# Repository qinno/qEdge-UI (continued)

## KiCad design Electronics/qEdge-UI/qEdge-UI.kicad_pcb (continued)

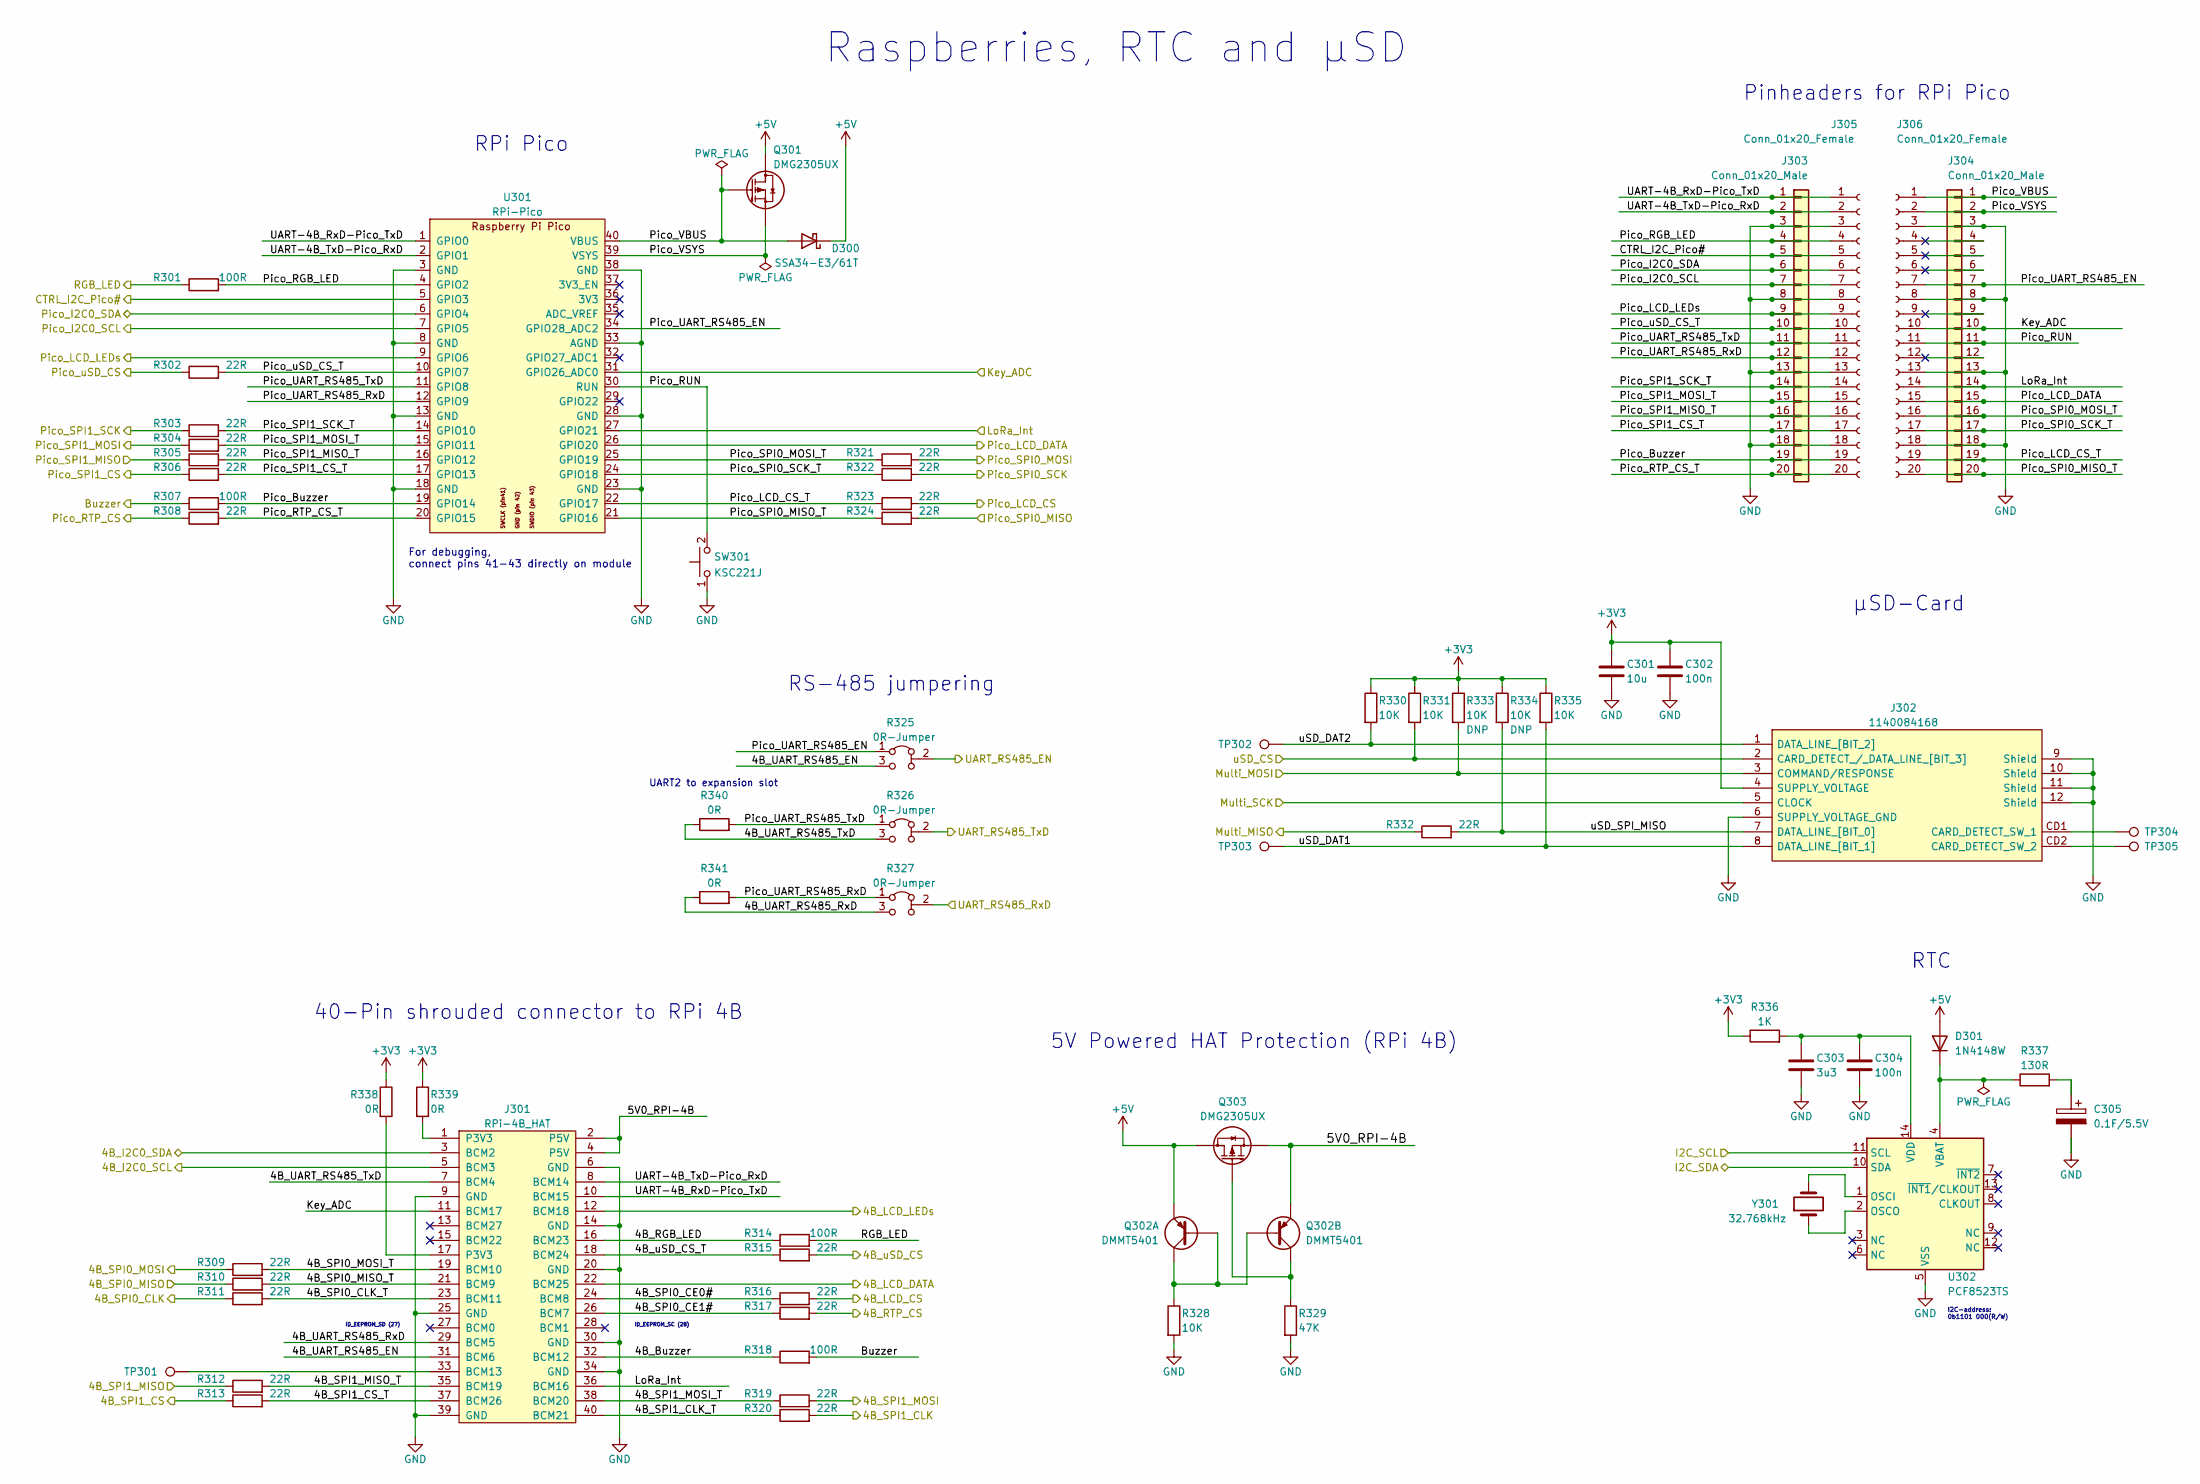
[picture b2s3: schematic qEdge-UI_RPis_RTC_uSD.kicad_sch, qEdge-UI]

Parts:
C301: 10u; C_0603_1608Metric
C302, C304: 100n; C_0603_1608Metric
C303: 3u3; C_0603_1608Metric
C305: 0.1F/5.5V; Elna_DX5R5H104U; Manufacturer_Part_Number DX-5R5H104U
D300: SSA34-E3/61T; D_SMA; Manufacturer_Part_Number SSA34-E3/61T
D301: 1N4148W; D_SOD-123; Manufacturer_Part_Number 1N4148W-E3
J301: RPi-4B_HAT; Wuerth_WR-BHD_61234020621; Manufacturer_Part_Number 61234020621
J302: 1140084168; Amphenol_1140084168; Manufacturer_Part_Number 1140084168
J303, J304: Conn_01x20_Male; PinHeader_1x20_P2.54mm_Vertical; Manufacturer_Part_Number MC34739
J305, J306: Conn_01x20_Female; PinSocket_1x20_P2.54mm_Vertical; Manufacturer_Part_Number 2212S-20SG-85
Q301, Q303: DMG2305UX; SOT-23; Manufacturer_Part_Number DMG2305UX-13
Q302: DMMT5401; SOT-23-6; Manufacturer_Part_Number DMMT5401-7-F
R301, R307, R314, R318: 100R; R_0603_1608Metric
R302, R303, R304, R305, R306, R308, R309, R310, R311, R312, R313, R315, R316, R317, R319, R320, R321, R322, R323, R324, R332: 22R; R_0603_1608Metric
R325, R326, R327: 0R-Jumper; 0603_3-pin-Jumper; Manufacturer_Part_Number RC0603FR-070RL
R328, R330, R331, R333, R334, R335: 10K; R_0603_1608Metric
R329: 47K; R_0603_1608Metric
R336: 1K; R_0603_1608Metric
R337: 130R; R_0603_1608Metric
R338, R339, R340, R341: 0R; R_0603_1608Metric
SW301: KSC221J; SW_Push_1P1T_NO_CK_KSC6xxJ; Manufacturer_Part_Number KSC221JLFS
TP301, TP302, TP303, TP304, TP305: TestPoint; TestPoint_Pad_D1.0mm
U301: RPi-Pico; RPi-Pico_THT_wo_Debug; Manufacturer_Part_Number Pico W
U302: PCF8523TS; TSSOP-14_4.4x5mm_P0.65mm
Y301: 32.768kHz; MicroCrystal_CM7V32768TBQA020; Manufacturer_Part_Number CM7V-T1A-Low-ESR-32.768k-7pF-10-TB-QA

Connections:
+3V3: C301.1, C302.1, J302.4 (SUPPLY_VOLTAGE), R330.1, R331.1, R333.1, R334.1, R335.1, R336.1, R338.1, R339.1; also elsewhere on the board
+5V: D300.1 (K), D301.2 (A), Q301.3 (D), Q302.6 (E), Q303.3 (D); also elsewhere on the board
/Comm. ifaces, Misc/4B_I2C0_SCL: J301.5 (BCM3); also elsewhere on the board
/Comm. ifaces, Misc/4B_I2C0_SDA: J301.3 (BCM2); also elsewhere on the board
/Comm. ifaces, Misc/4B_LCD_CS: R316.2; also elsewhere on the board
/Comm. ifaces, Misc/4B_LCD_DATA: J301.22 (BCM25); also elsewhere on the board
/Comm. ifaces, Misc/4B_LCD_LEDs: J301.12 (BCM18); also elsewhere on the board
/Comm. ifaces, Misc/4B_RTP_CS: R317.2; also elsewhere on the board
/Comm. ifaces, Misc/4B_SPI0_MISO: R310.1; also elsewhere on the board
/Comm. ifaces, Misc/4B_SPI0_MOSI: R309.1; also elsewhere on the board
/Comm. ifaces, Misc/4B_SPI0_SCK: R311.1; also elsewhere on the board
/Comm. ifaces, Misc/4B_SPI1_CS: R313.1; also elsewhere on the board
/Comm. ifaces, Misc/4B_SPI1_MISO: R312.1; also elsewhere on the board
/Comm. ifaces, Misc/4B_SPI1_MOSI: R319.2; also elsewhere on the board
/Comm. ifaces, Misc/4B_SPI1_SCK: R320.2; also elsewhere on the board
/Comm. ifaces, Misc/4B_uSD_CS: R315.2; also elsewhere on the board
/Comm. ifaces, Misc/I2C_SCL: U302.11 (SCL); also elsewhere on the board
/Comm. ifaces, Misc/I2C_SDA: U302.10 (SDA); also elsewhere on the board
/Comm. ifaces, Misc/Multi_MISO: R332.1; also elsewhere on the board
/Comm. ifaces, Misc/Multi_MOSI: J302.3 (COMMAND/RESPONSE), R333.2; also elsewhere on the board
/Comm. ifaces, Misc/Multi_SCK: J302.5 (CLOCK); also elsewhere on the board
/Comm. ifaces, Misc/Pico_LCD_CS: R323.2; also elsewhere on the board
/Comm. ifaces, Misc/Pico_RTP_CS: R308.1; also elsewhere on the board
/Comm. ifaces, Misc/Pico_SPI0_MISO: R324.2; also elsewhere on the board
/Comm. ifaces, Misc/Pico_SPI0_MOSI: R321.2; also elsewhere on the board
/Comm. ifaces, Misc/Pico_SPI0_SCK: R322.2; also elsewhere on the board
/Comm. ifaces, Misc/Pico_SPI1_CS: R306.1; also elsewhere on the board
/Comm. ifaces, Misc/Pico_SPI1_MISO: R305.1; also elsewhere on the board
/Comm. ifaces, Misc/Pico_SPI1_MOSI: R304.1; also elsewhere on the board
/Comm. ifaces, Misc/Pico_SPI1_SCK: R303.1; also elsewhere on the board
/Comm. ifaces, Misc/Pico_uSD_CS: R302.1; also elsewhere on the board
/Comm. ifaces, Misc/UART_RS485_EN: R325.2 (B); also elsewhere on the board
/Comm. ifaces, Misc/UART_RS485_RxD: R327.2 (B); also elsewhere on the board
/Comm. ifaces, Misc/UART_RS485_TxD: R326.2 (B); also elsewhere on the board
/Comm. ifaces, Misc/uSD_CS: J302.2 (CARD_DETECT_/_DATA_LINE_[BIT_3]), R331.2; also elsewhere on the board
/RPis, RTC, µSD/4B_Buzzer: J301.32 (BCM12), R318.1
/RPis, RTC, µSD/4B_RGB_LED: J301.16 (BCM23), R314.1
/RPis, RTC, µSD/4B_SPI0_CE0#: J301.24 (BCM8), R316.1
/RPis, RTC, µSD/4B_SPI0_CE1#: J301.26 (BCM7), R317.1
/RPis, RTC, µSD/4B_SPI0_CLK_T: J301.23 (BCM11), R311.2
/RPis, RTC, µSD/4B_SPI0_MISO_T: J301.21 (BCM9), R310.2
/RPis, RTC, µSD/4B_SPI0_MOSI_T: J301.19 (BCM10), R309.2
/RPis, RTC, µSD/4B_SPI1_CLK_T: J301.40 (BCM21), R320.1
/RPis, RTC, µSD/4B_SPI1_CS_T: J301.37 (BCM26), R313.2
/RPis, RTC, µSD/4B_SPI1_MISO_T: J301.35 (BCM19), R312.2
/RPis, RTC, µSD/4B_SPI1_MOSI_T: J301.38 (BCM20), R319.1
/RPis, RTC, µSD/4B_UART_RS485_EN: J301.31 (BCM6), R325.3 (C)
/RPis, RTC, µSD/4B_UART_RS485_RxD: J301.29 (BCM5), R327.3 (C), R341.1
/RPis, RTC, µSD/4B_UART_RS485_TxD: J301.7 (BCM4), R326.3 (C), R340.1
/RPis, RTC, µSD/4B_uSD_CS_T: J301.18 (BCM24), R315.1
/RPis, RTC, µSD/5V0_RPI-4B: J301.2 (P5V), J301.4 (P5V), Q302.5 (E), Q303.2 (S)
/RPis, RTC, µSD/Buzzer: R307.1, R318.2; also elsewhere on the board
/RPis, RTC, µSD/CTRL_I2C_Pico#: J303.5, J305.5, U301.5 (GPIO3); also elsewhere on the board
/RPis, RTC, µSD/Key_ADC: J301.11 (BCM17), J304.10, J306.10, U301.31 (GPIO26_ADC0); also elsewhere on the board
/RPis, RTC, µSD/LoRa_Int: J301.36 (BCM16), J304.14, J306.14, U301.27 (GPIO21); also elsewhere on the board
/RPis, RTC, µSD/Pico_Buzzer: J303.19, J305.19, R307.2, U301.19 (GPIO14)
/RPis, RTC, µSD/Pico_I2C0_SCL: J303.7, J305.7, U301.7 (GPIO5); also elsewhere on the board
/RPis, RTC, µSD/Pico_I2C0_SDA: J303.6, J305.6, U301.6 (GPIO4); also elsewhere on the board
/RPis, RTC, µSD/Pico_LCD_CS_T: J304.19, J306.19, R323.1, U301.22 (GPIO17)
/RPis, RTC, µSD/Pico_LCD_DATA: J304.15, J306.15, U301.26 (GPIO20); also elsewhere on the board
/RPis, RTC, µSD/Pico_LCD_LEDs: J303.9, J305.9, U301.9 (GPIO6); also elsewhere on the board
/RPis, RTC, µSD/Pico_RGB_LED: J303.4, J305.4, R301.2, U301.4 (GPIO2)
/RPis, RTC, µSD/Pico_RTP_CS_T: J303.20, J305.20, R308.2, U301.20 (GPIO15)
/RPis, RTC, µSD/Pico_RUN: J304.11, J306.11, SW301.2, U301.30 (RUN)
/RPis, RTC, µSD/Pico_SPI0_MISO_T: J304.20, J306.20, R324.1, U301.21 (GPIO16)
/RPis, RTC, µSD/Pico_SPI0_MOSI_T: J304.16, J306.16, R321.1, U301.25 (GPIO19)
/RPis, RTC, µSD/Pico_SPI0_SCK_T: J304.17, J306.17, R322.1, U301.24 (GPIO18)
/RPis, RTC, µSD/Pico_SPI1_CS_T: J303.17, J305.17, R306.2, U301.17 (GPIO13)
/RPis, RTC, µSD/Pico_SPI1_MISO_T: J303.16, J305.16, R305.2, U301.16 (GPIO12)
/RPis, RTC, µSD/Pico_SPI1_MOSI_T: J303.15, J305.15, R304.2, U301.15 (GPIO11)
/RPis, RTC, µSD/Pico_SPI1_SCK_T: J303.14, J305.14, R303.2, U301.14 (GPIO10)
/RPis, RTC, µSD/Pico_UART_RS485_EN: J304.7, J306.7, R325.1 (A), U301.34 (GPIO28_ADC2)
/RPis, RTC, µSD/Pico_UART_RS485_RxD: J303.12, J305.12, R327.1 (A), R341.2, U301.12 (GPIO9)
/RPis, RTC, µSD/Pico_UART_RS485_TxD: J303.11, J305.11, R326.1 (A), R340.2, U301.11 (GPIO8)
/RPis, RTC, µSD/Pico_VBUS: D300.2 (A), J304.1, J306.1, Q301.1 (G), U301.40 (VBUS)
/RPis, RTC, µSD/Pico_VSYS: J304.2, J306.2, Q301.2 (S), U301.39 (VSYS)
/RPis, RTC, µSD/Pico_uSD_CS_T: J303.10, J305.10, R302.2, U301.10 (GPIO7)
/RPis, RTC, µSD/RGB_LED: R301.1, R314.2; also elsewhere on the board
/RPis, RTC, µSD/UART-4B_RxD-Pico_TxD: J301.10 (BCM15), J303.1, J305.1, U301.1 (GPIO0)
/RPis, RTC, µSD/UART-4B_TxD-Pico_RxD: J301.8 (BCM14), J303.2, J305.2, U301.2 (GPIO1)
/RPis, RTC, µSD/uSD_DAT1: J302.8 (DATA_LINE_[BIT_1]), R335.2, TP303.1
/RPis, RTC, µSD/uSD_DAT2: J302.1 (DATA_LINE_[BIT_2]), R330.2, TP302.1
/RPis, RTC, µSD/uSD_SPI_MISO: J302.7 (DATA_LINE_[BIT_0]), R332.2, R334.2
GND: C301.2, C302.2, C303.2, C304.2, C305.1, J301.6 (GND), J301.9 (GND), J301.14 (GND), J301.20 (GND), J301.25 (GND), J301.30 (GND), J301.34 (GND), J301.39 (GND), J302.6 (SUPPLY_VOLTAGE_GND), J302.9 (Shield), J302.10 (Shield), J302.11 (Shield), J302.12 (Shield), J303.3, J303.8, J303.13, J303.18, J304.3, J304.8, J304.13, J304.18, J305.3, J305.8, J305.13, J305.18, J306.3, J306.8, J306.13, J306.18, R328.2, R329.2, SW301.1, U301.3 (GND), U301.8 (GND), U301.13 (GND), U301.18 (GND), U301.23 (GND), U301.28 (GND), U301.33 (AGND), U301.38 (GND), U302.5 (VSS); also elsewhere on the board
unnamed: C303.1, C304.1, R336.2, U302.14 (VDD)
unnamed: C305.2, R337.2
unnamed: D301.1 (K), R337.1, U302.4 (VBAT)
unnamed: J301.1 (P3V3), R339.2
unnamed: J301.17 (P3V3), R338.2
unnamed: J301.33 (BCM13), TP301.1
unnamed: J302.CD1 (CARD_DETECT_SW_1), TP304.1
unnamed: J302.CD2 (CARD_DETECT_SW_2), TP305.1
unnamed: Q302.1 (C), Q302.2 (B), Q302.3 (B), R328.1
unnamed: Q302.4 (C), Q303.1 (G), R329.1
unnamed: U302.1 (OSCI), Y301.2
unnamed: U302.2 (OSCO), Y301.1

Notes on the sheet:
Pinheaders for RPi Pico
ID_EEPROM_SC (28)
RS-485 jumpering
For debugging, connect pins 41-43 directly on module
µSD-Card
ID_EEPROM_SD (27)
RTC
RPi Pico
5V Powered HAT Protection (RPi 4B)
I2C-address: 0b1101 000(R/W)
UART2 to expansion slot
40-Pin shrouded connector to RPi 4B
Raspberries, RTC and µSD

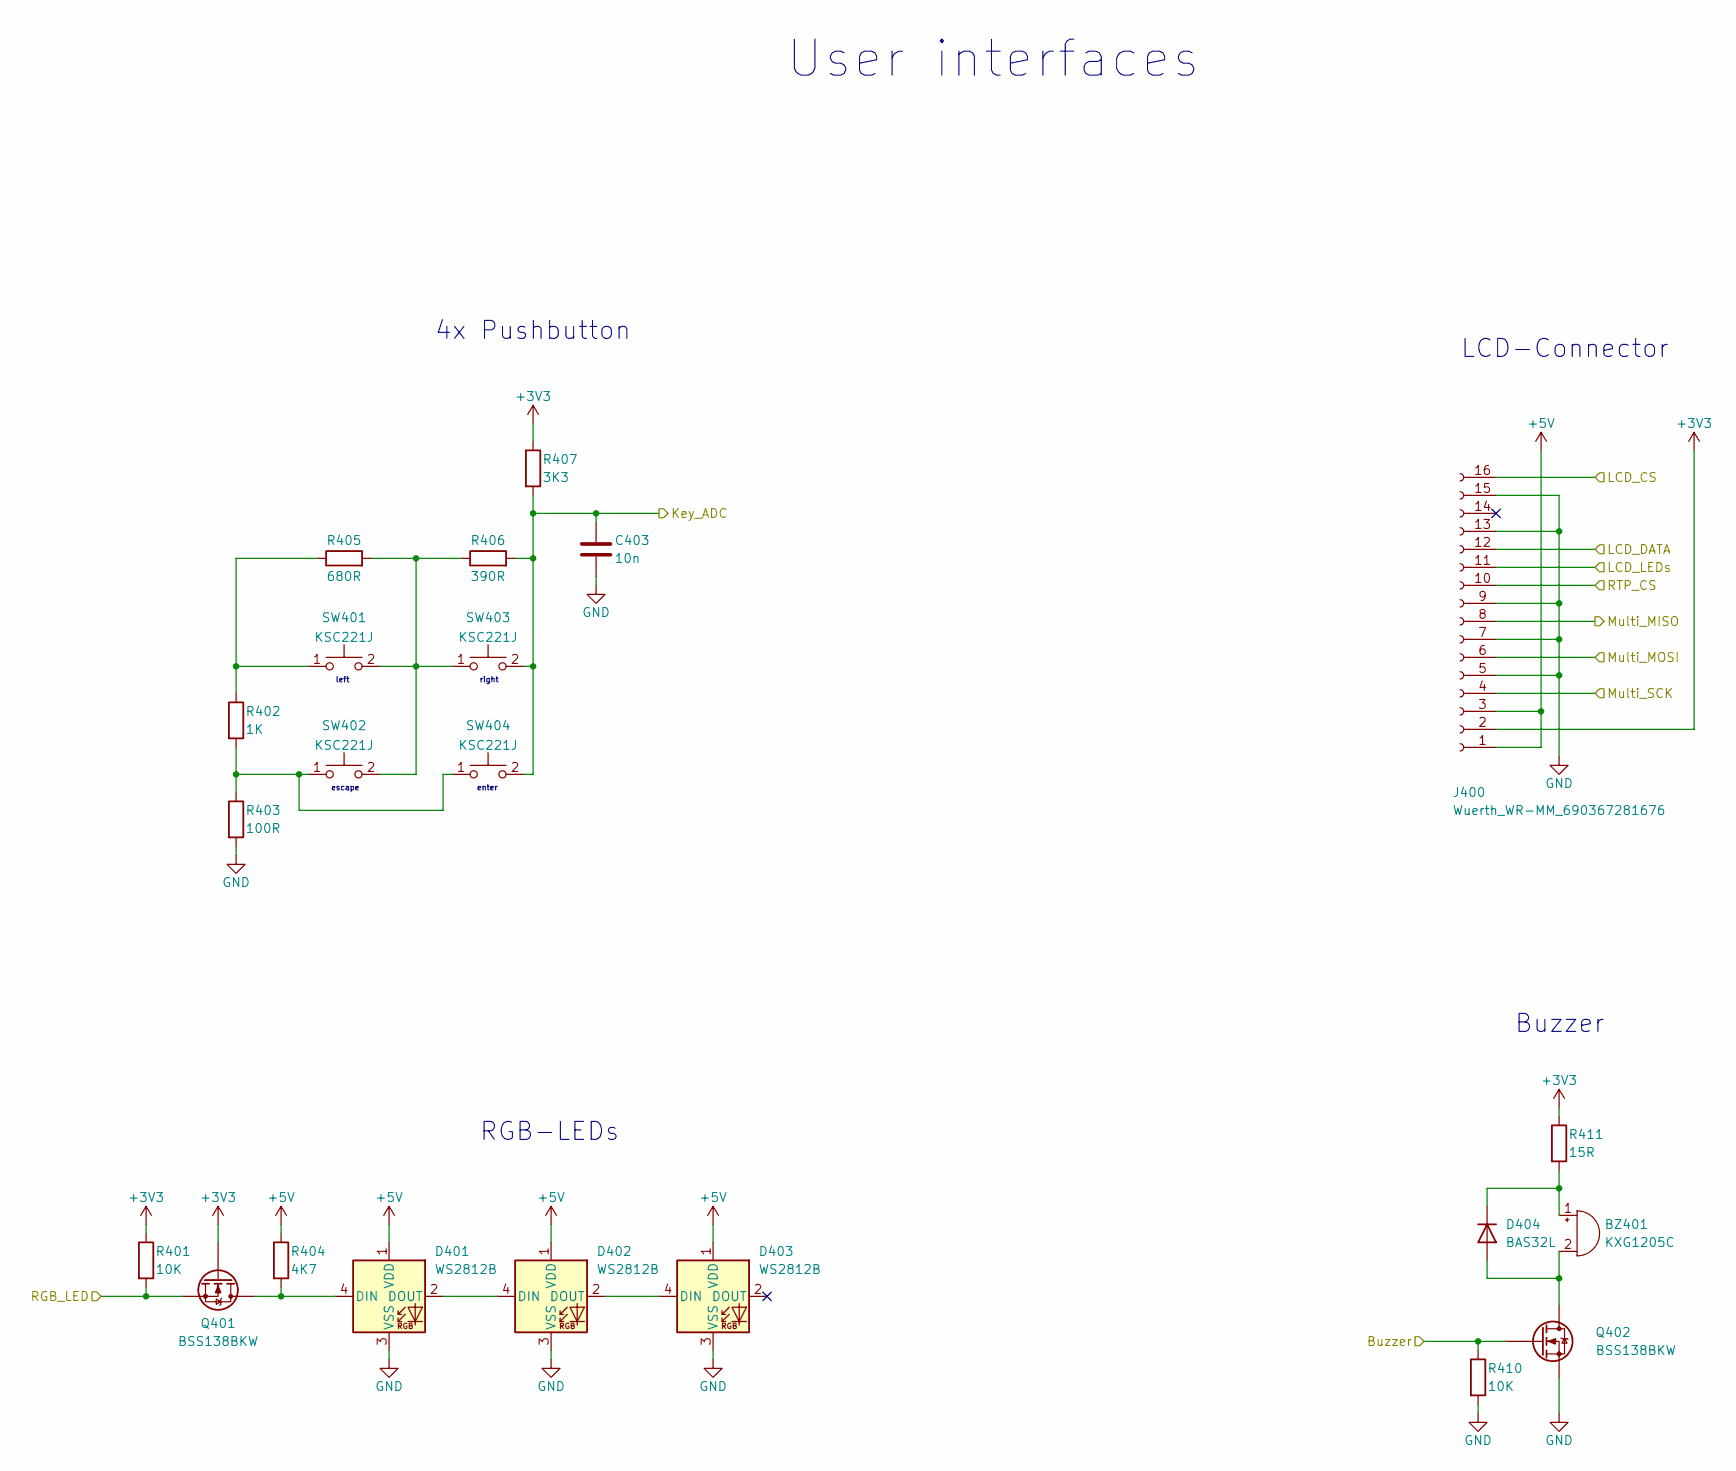
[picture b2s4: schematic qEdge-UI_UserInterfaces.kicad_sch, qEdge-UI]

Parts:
BZ401: KXG1205C; Buzzer_12x9.5RM7.6; Manufacturer_Part_Number KXG1205C
C403: 10n; C_0603_1608Metric
D401, D402, D403: WS2812B; LED_WS2812B_PLCC4_5.0x5.0mm_P3.2mm; Manufacturer_Part_Number WS2812B
D404: BAS32L; D_MiniMELF; Manufacturer_Part_Number BAS32L,115
J400: Wuerth_WR-MM_690367281676; Manufacturer_Part_Number 690367281676
Q401, Q402: BSS138BKW; SOT-323_SC-70; Manufacturer_Part_Number BSS138BKW,115
R401, R410: 10K; R_0603_1608Metric
R402: 1K; R_0603_1608Metric
R403: 100R; R_0603_1608Metric
R404: 4K7; R_0603_1608Metric
R405: 680R; R_0603_1608Metric
R406: 390R; R_0603_1608Metric
R407: 3K3; R_0603_1608Metric
R411: 15R; R_0805_2012Metric
SW401, SW402, SW403, SW404: KSC221J; SW_Push_1P1T_NO_CK_KSC6xxJ; Manufacturer_Part_Number KSC221JLFS

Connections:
+3V3: J400.2, Q401.1 (G), R401.1, R407.1, R411.1; also elsewhere on the board
+5V: D401.1 (VDD), D402.1 (VDD), D403.1 (VDD), J400.1, J400.3, R404.1; also elsewhere on the board
/Comm. ifaces, Misc/LCD_CS: J400.16; also elsewhere on the board
/Comm. ifaces, Misc/LCD_DATA: J400.12; also elsewhere on the board
/Comm. ifaces, Misc/LCD_LEDs: J400.11; also elsewhere on the board
/Comm. ifaces, Misc/Multi_MISO: J400.8; also elsewhere on the board
/Comm. ifaces, Misc/Multi_MOSI: J400.6; also elsewhere on the board
/Comm. ifaces, Misc/Multi_SCK: J400.4; also elsewhere on the board
/Comm. ifaces, Misc/RTP_CS: J400.10; also elsewhere on the board
/RPis, RTC, µSD/Buzzer: Q402.1 (G), R410.1; also elsewhere on the board
/RPis, RTC, µSD/Key_ADC: C403.1, R406.2, R407.2, SW403.2, SW404.2; also elsewhere on the board
/RPis, RTC, µSD/RGB_LED: Q401.2 (S), R401.2; also elsewhere on the board
GND: C403.2, D401.3 (VSS), D402.3 (VSS), D403.3 (VSS), J400.5, J400.7, J400.9, J400.13, J400.15, Q402.2 (S), R403.2, R410.2; also elsewhere on the board
unnamed: BZ401.1 (-), D404.1 (K), R411.2
unnamed: BZ401.2 (+), D404.2 (A), Q402.3 (D)
unnamed: D401.2 (DOUT), D402.4 (DIN)
unnamed: D401.4 (DIN), Q401.3 (D), R404.2
unnamed: D402.2 (DOUT), D403.4 (DIN)
unnamed: R402.1, R405.1, SW401.1
unnamed: R402.2, R403.1, SW402.1, SW404.1
unnamed: R405.2, R406.1, SW401.2, SW402.2, SW403.1

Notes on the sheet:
right
left
escape
Buzzer
User interfaces
LCD-Connector
4x Pushbutton
enter
RGB-LEDs

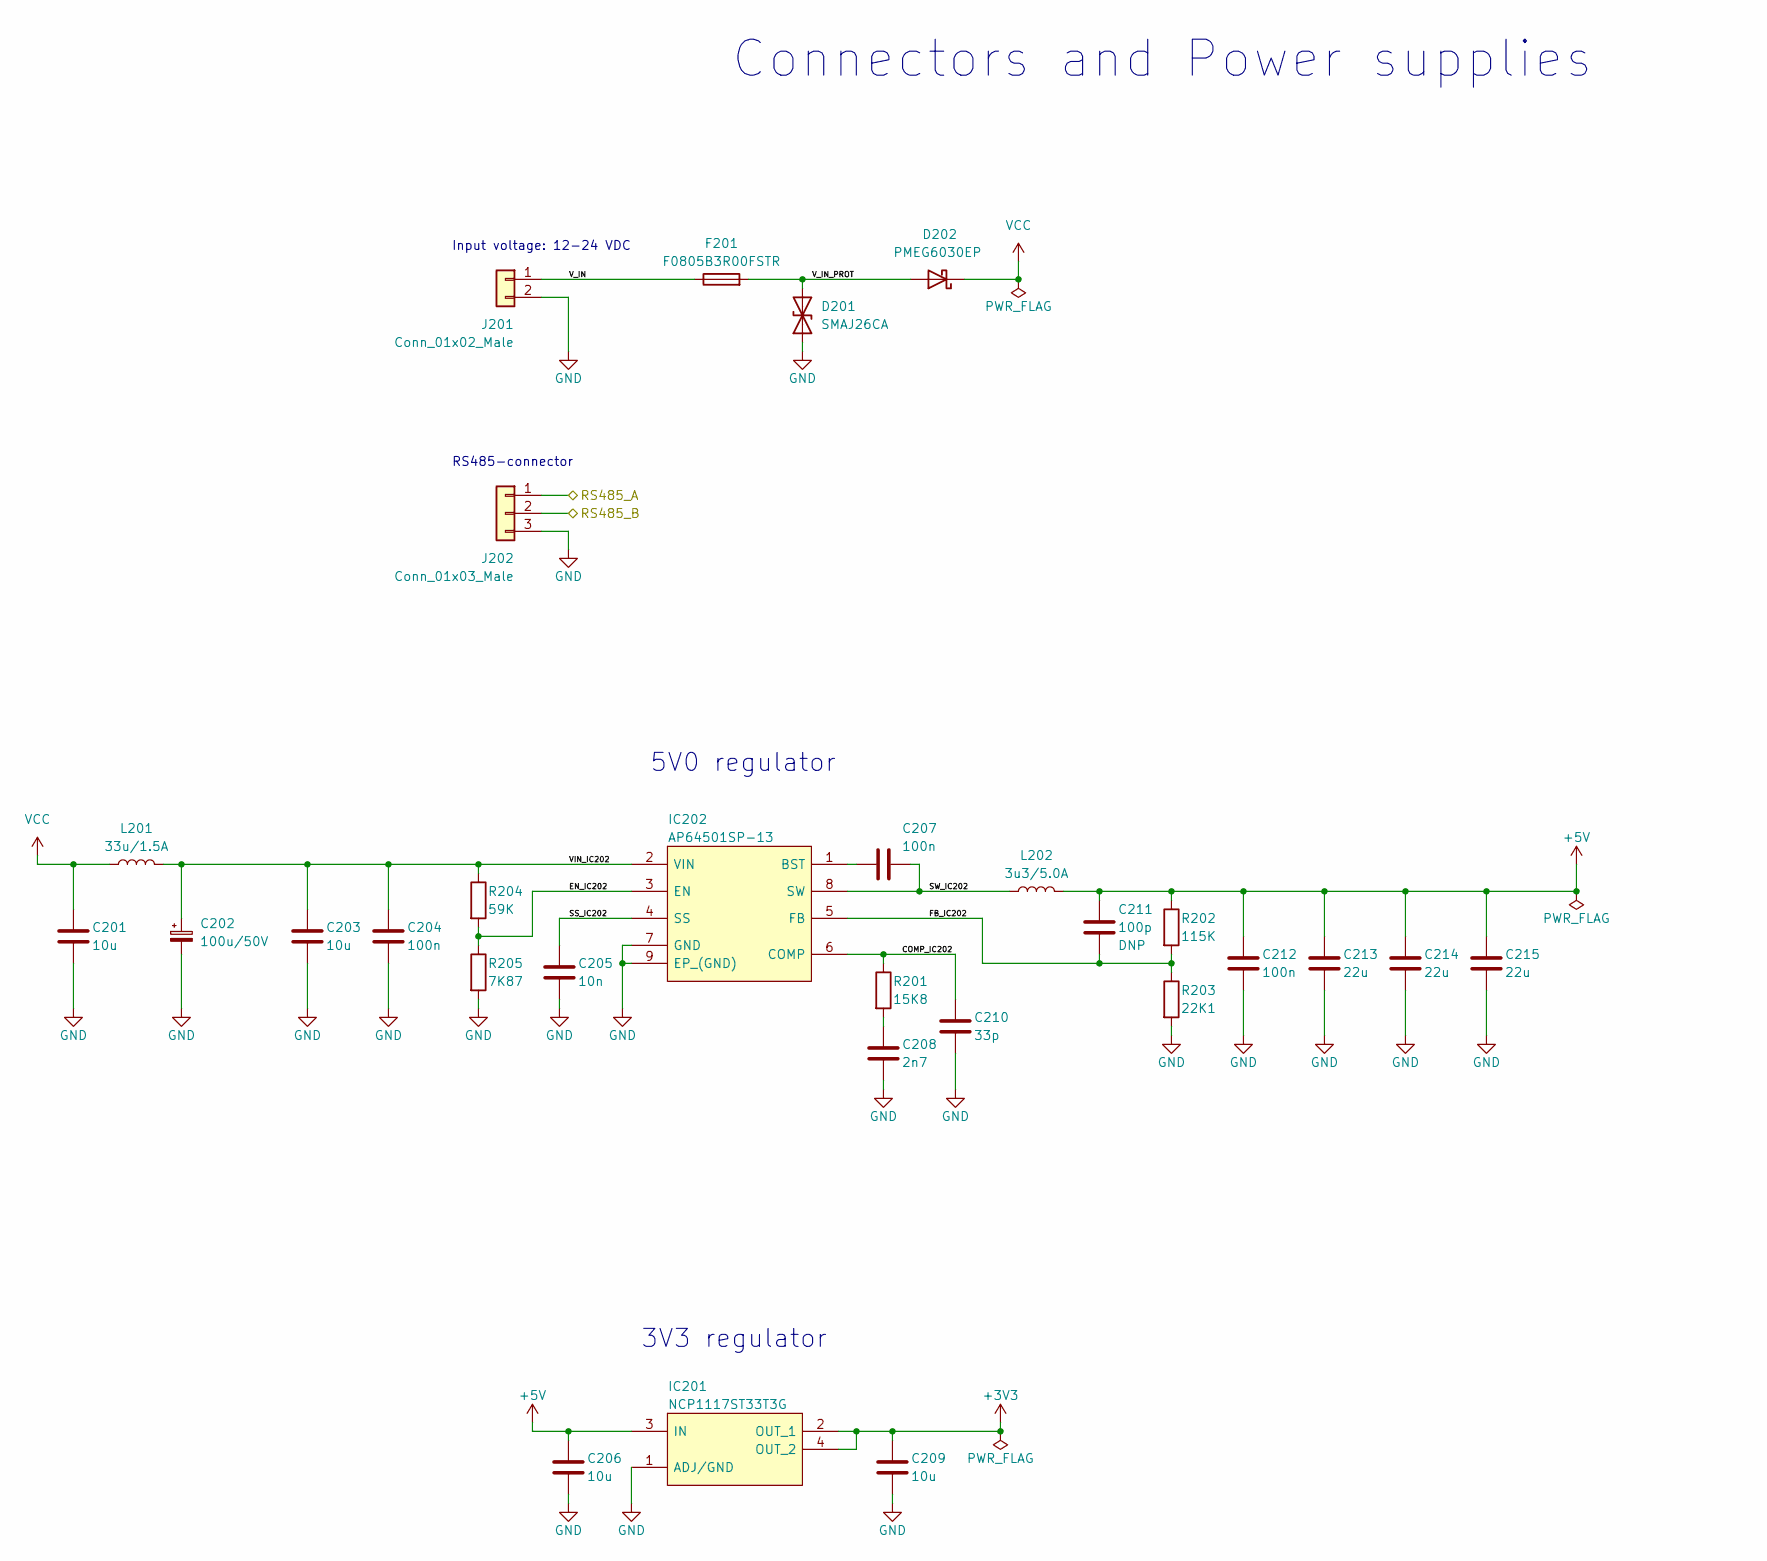
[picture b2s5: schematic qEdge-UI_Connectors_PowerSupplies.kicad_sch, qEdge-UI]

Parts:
C201, C203: 10u; C_0805_2012Metric
C202: 100u/50V; CP_Elec_8x10.5; Manufacturer_Part_Number 865080653016
C204, C207, C212: 100n; C_0603_1608Metric
C205: 10n; C_0603_1608Metric
C206, C209: 10u; C_0603_1608Metric
C208: 2n7; C_0603_1608Metric
C210: 33p; C_0603_1608Metric
C211: 100p; C_0603_1608Metric
C213, C214, C215: 22u; C_0805_2012Metric
D201: SMAJ26CA; D_SMA_bipolar; Manufacturer_Part_Number SMAJ26CA
D202: PMEG6030EP; D_SOD-128; Manufacturer_Part_Number PMEG6030EP,115
F201: F0805B3R00FSTR; Fuse_0805_2012Metric; Manufacturer_Part_Number F0805B3R00FSTR
IC201: NCP1117ST33T3G; SOT230P700X180-4N; Manufacturer_Part_Number NCP1117ST33T3G
IC202: AP64501SP-13; SOIC127P600X163-9N; Manufacturer_Part_Number AP64501SP-13
J201: Conn_01x02_Male; PhoenixContact_MC_1,5_2-G-3.5_1x02_P3.50mm_Horizontal; Manufacturer_Part_Number MC 1,5/ 2-G-3,5 - 1844210
J202: Conn_01x03_Male; PhoenixContact_MC_1,5_3-G-3.5_1x03_P3.50mm_Horizontal; Manufacturer_Part_Number MC 1,5/ 3-G-3,5 - 1844223
L201: 33u/1.5A; Murata_1255AY100MP3; Manufacturer_Part_Number 1255AY-330M=P3
L202: 3u3/5.0A; Abracon_ASPI0530LR3R3MT2; Manufacturer_Part_Number ASPI-0530LR-3R3M-T2
R201: 15K8; R_0603_1608Metric
R202: 115K; R_0603_1608Metric
R203: 22K1; R_0603_1608Metric
R204: 59K; R_0603_1608Metric
R205: 7K87; R_0603_1608Metric

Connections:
+3V3: C209.1, IC201.2 (OUT_1), IC201.4 (OUT_2); also elsewhere on the board
+5V: C206.1, C211.1, C212.1, C213.1, C214.1, C215.1, IC201.3 (IN), L202.2, R202.1; also elsewhere on the board
/Comm. ifaces, Misc/RS485_A: J202.1; also elsewhere on the board
/Comm. ifaces, Misc/RS485_B: J202.2; also elsewhere on the board
/Connectors, Power supplies/COMP_IC202: C210.1, IC202.6 (COMP), R201.1
/Connectors, Power supplies/EN_IC202: IC202.3 (EN), R204.2, R205.1
/Connectors, Power supplies/FB_IC202: C211.2, IC202.5 (FB), R202.2, R203.1
/Connectors, Power supplies/SS_IC202: C205.1, IC202.4 (SS)
/Connectors, Power supplies/SW_IC202: C207.1, IC202.8 (SW), L202.1
/Connectors, Power supplies/VIN_IC202: C202.1, C203.1, C204.1, IC202.2 (VIN), L201.2, R204.1
/Connectors, Power supplies/V_IN: F201.1, J201.1
/Connectors, Power supplies/V_IN_PROT: D201.2 (A2), D202.2 (A), F201.2
GND: C201.2, C202.2, C203.2, C204.2, C205.2, C206.2, C208.2, C209.2, C210.2, C212.2, C213.2, C214.2, C215.2, D201.1 (A1), IC201.1 (ADJ/GND), IC202.7 (GND), IC202.9 (EP_(GND)), J201.2, J202.3, R203.2, R205.2; also elsewhere on the board
unnamed: C207.2, IC202.1 (BST)
unnamed: C208.1, R201.2
VCC: C201.1, D202.1 (K), L201.1

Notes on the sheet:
RS485-connector
Connectors and Power supplies
3V3 regulator
5V0 regulator
Input voltage: 12-24 VDC

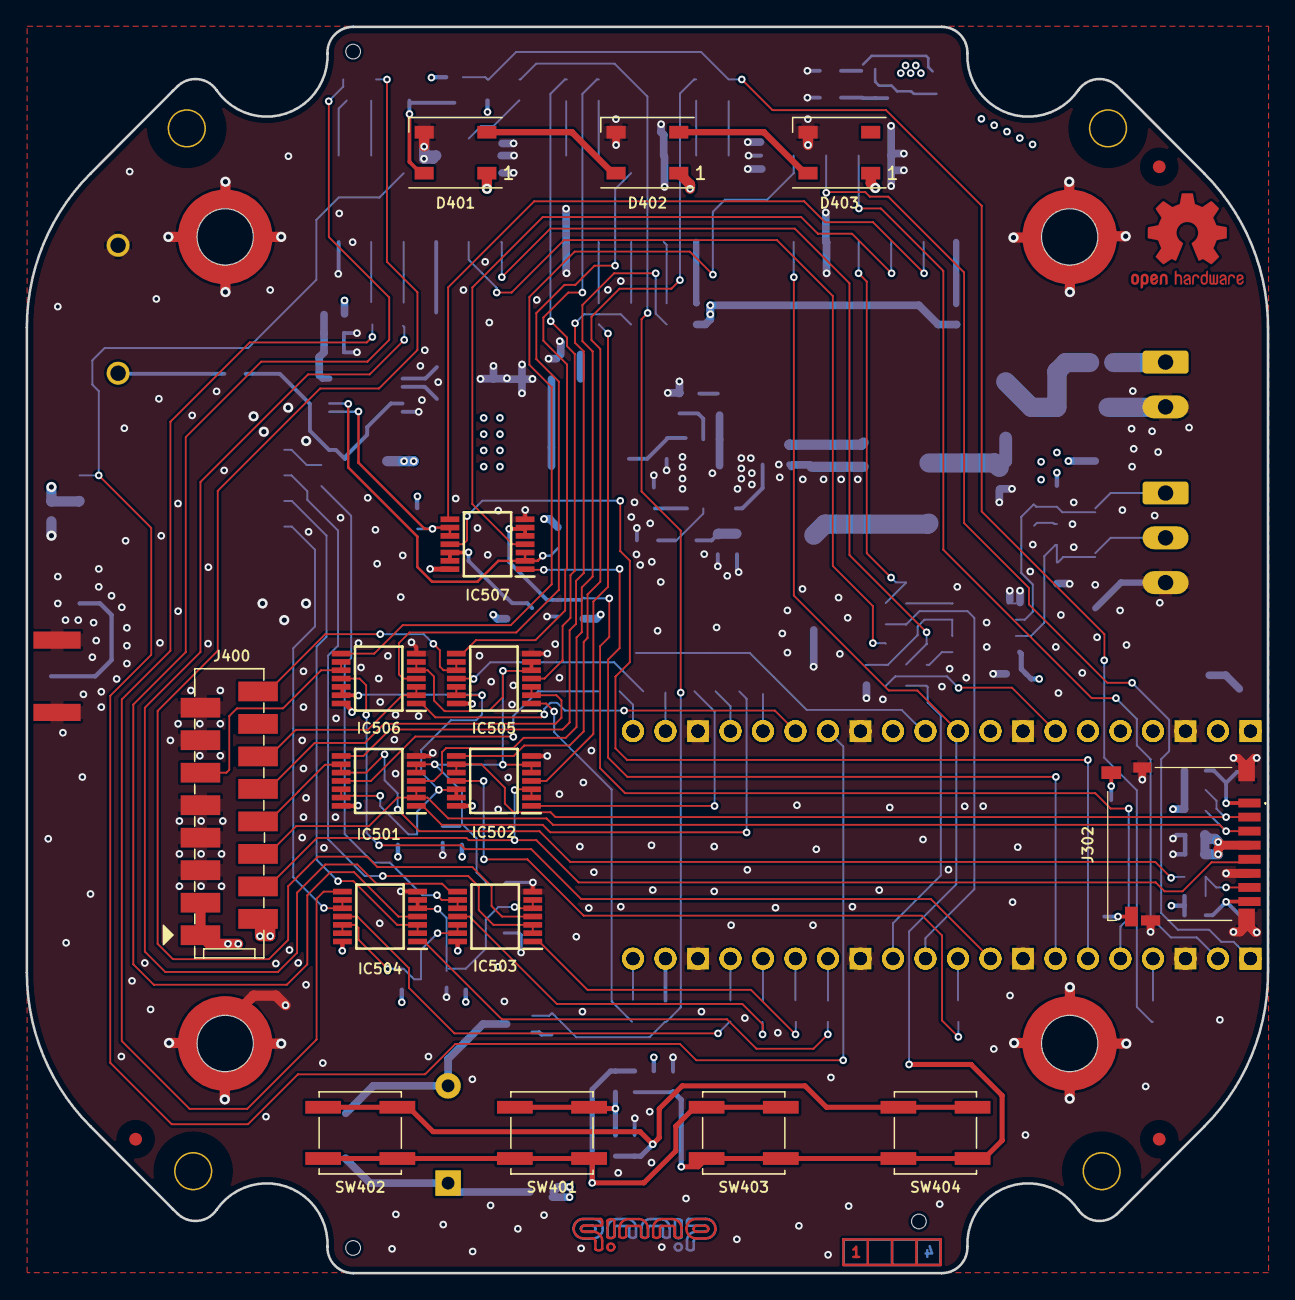
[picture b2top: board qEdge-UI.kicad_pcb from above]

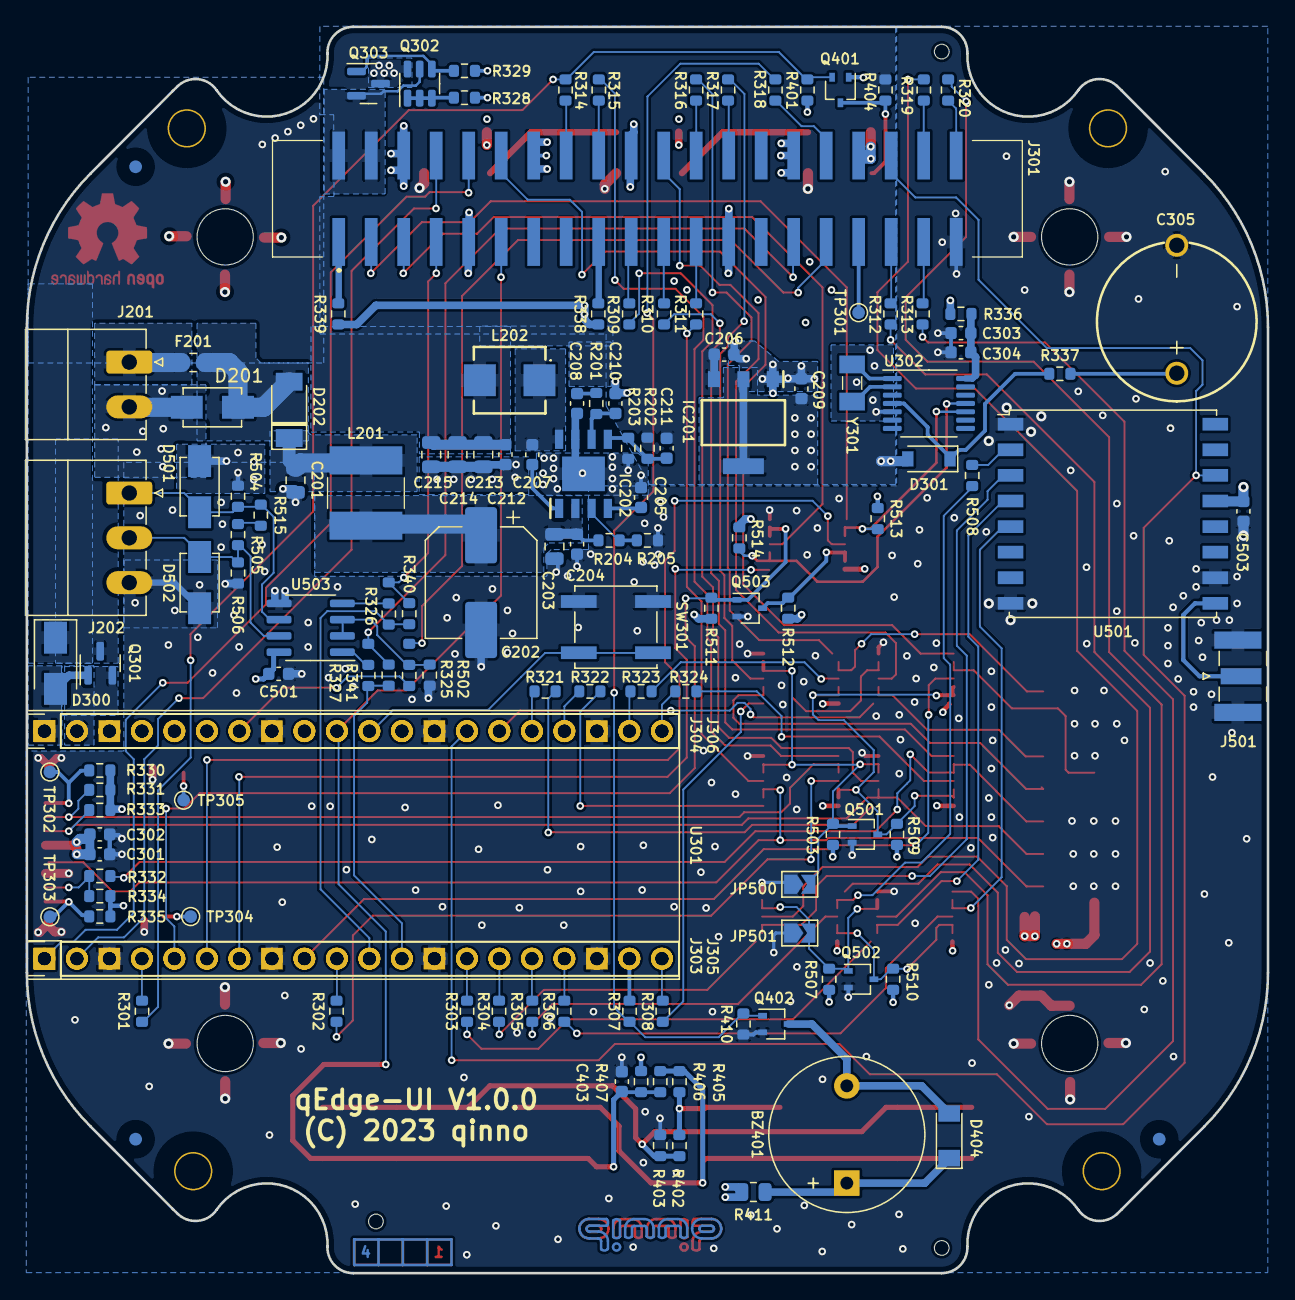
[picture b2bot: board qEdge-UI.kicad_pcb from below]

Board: 4 copper layers, 97.0 x 97.4 mm, 170 parts (138 on the bottom side), 133 nets.

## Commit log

2023-08-08 initial commit.
2023-08-08 move Software to subdirectory, fix libraries.
2023-08-08 Add electronics and mechanics
2023-08-16 change preview path to local path
2023-08-16 changed path to local path
2023-08-16 fix images
2023-08-23 Update README.md
    Fixed Readme.md links and other typos for go live (making repo public)
2023-09-12 Readme.md split in more parts and placed in main and electronics, mechanics and software subfolder) for better understanding.
2023-09-12 Fixed some typos + changes absolut path name to releativ path names
2023-09-12 Renaming software subfolder and file names for a better integration of the git repo in the arduino software development environment.
2023-09-12 Created own Readme.md for the software folder
2023-09-13 Readme.md ready for release + Removed Quick start guide and corresponding binaries to reduce copyright dependencies
2023-09-13 Main Readme.md and Software/Readme.md ready for release tagging
2023-09-14 added READMEs for Mechanic and Electronic added License in the Electronic schematics restructured Mechanics for better readability and reproducibility
2023-09-14 changed Mechanics link description
2023-09-15 slow start without uSD fixed tested with 4-32GB uSD-cards FAT32
2023-09-20 Update license information for images and libraries/TFT_eSPI/User_Setup for legal clarification
2023-09-23 Create Bambu Studio Print File
    Print File for Bambulab Printers/Bambu Studio added.
2023-09-23 BambuLab A1 Print File
    Added a printfile for BambuLab A1 for BambuStudio 1.7.6.92
2023-09-23 Added describing images
    Example images for print data added.
    Overview images for BambuStudio print data added
    +small fix to print data "p1-x1"
2023-09-23 update mech read.me
    Extension of the description with further print data
2023-12-07 added Varmecos donation of material
2025-02-18 Update to PICO2/RP2350
